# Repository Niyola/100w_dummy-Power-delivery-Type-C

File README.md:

USB Type-C Power Delivery Tester

A USB-C Power Delivery tester and 100W dummy load, built as part of my Master's thesis at Brno University of Technology.

The board negotiates a USB-PD contract with any USB-C charger, power bank, or laptop, requests different voltages (5V, 9V, 12V, 15V, 20V), and measures what is actually being delivered in real time. It handles up to 100W.

What's inside

The STM32F072CB runs the USB-PD protocol stack. The FUSB302B from onsemi handles the CC line communication. The INA237 from Texas Instruments measures voltage and current on VBUS bidirectionally. It is a 4-layer board, roughly 100mm by 60mm, with dedicated inner planes for ground and 3.3V.

References I used

Twonkie v2.0 by dojoe — https://github.com/dojoe/Twonkie/tree/master
An open source USB-PD sniffer. I followed its approach for the FUSB302B wiring and the CC line level shifting.

TI TPS25751EVM — https://www.ti.com/tool/TPS25751EVM
Texas Instruments' official USB-PD evaluation board. I used it as a reference for the high-current VBUS layout and current sensing.

What I changed

I use a single INA237 for bidirectional current sensing instead of two separate chips. I added a screw terminal output so the board works as a dummy load tester, not just a sniffer. I redesigned the stackup as 4 layers with full ground and 3.3V planes for better power integrity at 100W. I also added test points for bring-up.

About me

Eniola Adesuyi, M.Sc. Communications and Networking, Brno University of Technology. Supervised by Ing. Ondřej Krajsa, Ph.D.

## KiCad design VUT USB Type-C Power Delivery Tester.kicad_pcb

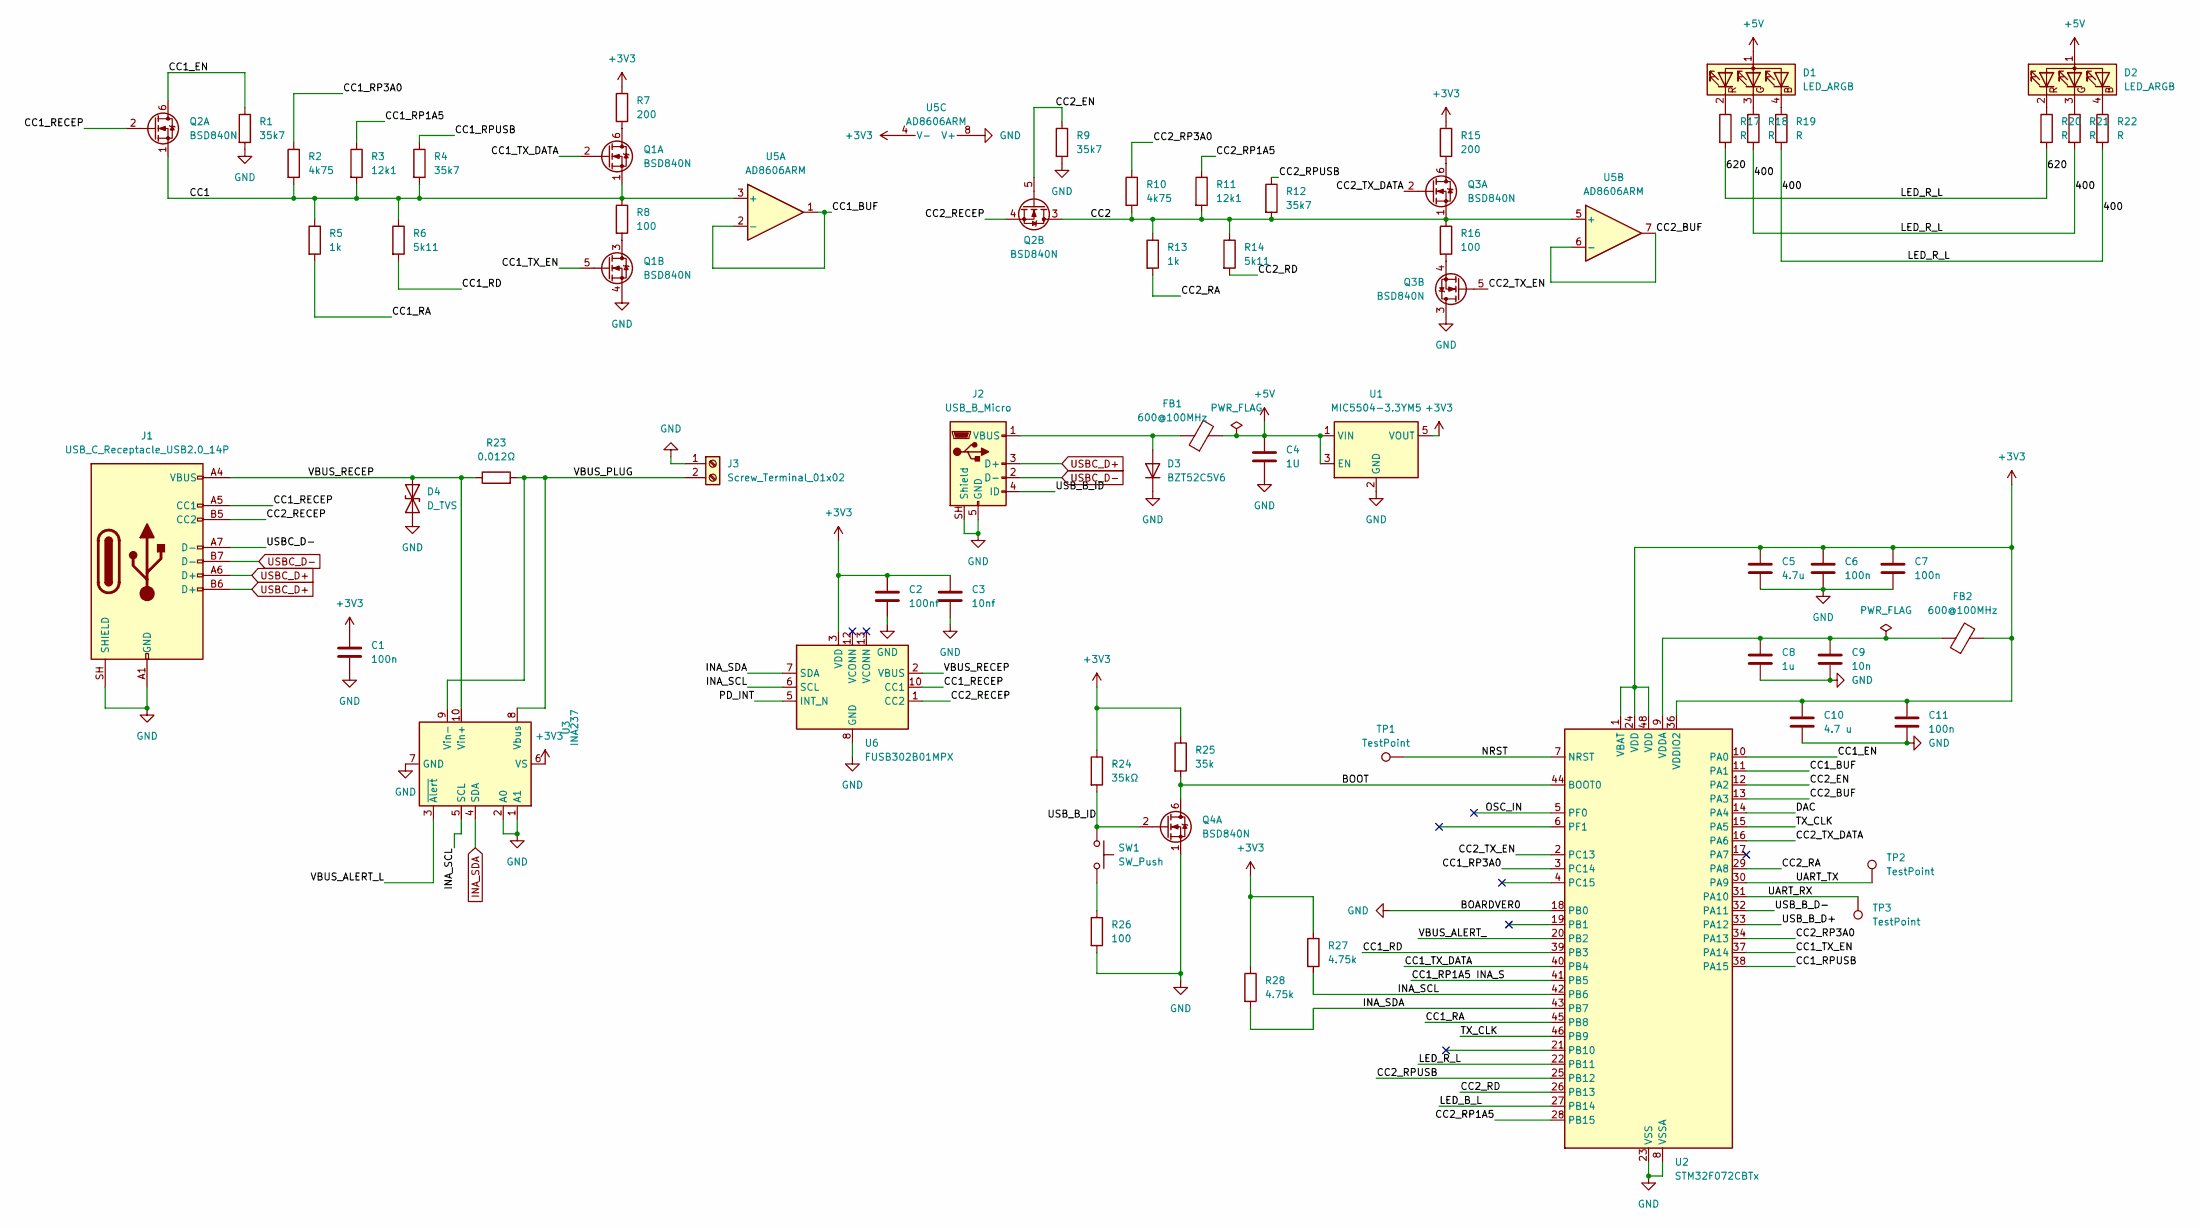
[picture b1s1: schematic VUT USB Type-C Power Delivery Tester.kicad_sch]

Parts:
C1, C6, C11: 100n; C_0402_1005Metric
C2: 100nf; C_0805_2012Metric
C3: 10nf; C_0402_1005Metric
C4: 1U; C_0402_1005Metric
C5: 4.7u; C_0402_1005Metric
C7: 100n; C_0805_2012Metric
C8: 1u; C_0402_1005Metric
C9: 10n; C_0402_1005Metric
C10: 4.7 u; C_0805_2012Metric
D1, D2: LED_ARGB; LED_Wurth_150044M155260
D3: BZT52C5V6; D_SOD-123
D4: D_TVS; D_SMB
FB1, FB2: 600@100MHz; L_0603_1608Metric
J1: USB_C_Receptacle_USB2.0_14P; USB_C_Receptacle_XKB_U262-16XN-4BVC11
J2: USB_B_Micro; USB_Micro-B_Molex-105017-0001
J3: Screw_Terminal_01x02; TerminalBlock_Phoenix_PT-1,5-2-3.5-H_1x02_P3.50mm_Horizontal
Q1, Q2, Q3, Q4: BSD840N; SOT-363_SC-70-6
R1, R4, R9, R12: 35k7; R_0402_1005Metric
R2, R10: 4k75; R_0402_1005Metric
R3, R11: 12k1; R_0402_1005Metric
R5, R13: 1k; R_0402_1005Metric
R6, R14: 5k11; R_0402_1005Metric
R7, R15: 200; R_0402_1005Metric
R8, R16, R26: 100; R_0402_1005Metric
R17, R18, R19, R20, R21, R22: R; R_0402_1005Metric
R23: 0.012Ω; R_0402_1005Metric
R24: 35kΩ; R_0402_1005Metric
R25: 35k; R_0402_1005Metric
R27, R28: 4.75k; R_0402_1005Metric
SW1: SW_Push; SW_SPST_PTS645Sx43SMTR92
TP1, TP2, TP3: TestPoint; TestPoint_Pad_1.0x1.0mm
U1: MIC5504-3.3YM5; SOT-23-5
U2: STM32F072CBTx; LQFP-48_7x7mm_P0.5mm
U3: INA237; TSSOP-10_3x3mm_P0.5mm
U5: AD8606ARM; MSOP-8_3x3mm_P0.65mm
U6: FUSB302B01MPX; WQFN-14-1EP_2.5x2.5mm_P0.5mm_EP1.45x1.45mm

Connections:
+3V3: C1.1, C2.1, C3.1, C5.1, C6.1, C7.1, C10.1, C11.1, FB2.2, R7.1, R15.1, R24.1, R25.1, R27.1, R28.1, U1.5 (VOUT), U2.1 (VBAT), U2.24 (VDD), U2.36 (VDDIO2), U2.48 (VDD), U3.6 (VS), U5.4 (V-), U6.3 (VDD), U6.4 (VDD)
+5V: C4.1, D1.1 (A), D2.1 (A), FB1.2, U1.1 (VIN), U1.3 (EN)
/400: R17.2, R18.2, R19.2, R20.2, R21.2, R22.2, U2.22 (PB11)
/BOOT: Q4.6 (D), R25.2, U2.44 (BOOT0)
/CC1: Q1.1 (S), Q2.1 (S), R2.2, R3.2, R4.2, R5.1, R6.1, R8.1, U5.3 (+)
/CC1_BUF: U2.11 (PA1), U5.1, U5.2 (-)
/CC1_EN: Q2.6 (D), R1.1, U2.10 (PA0)
/CC1_RA: R5.2, U2.45 (PB8)
/CC1_RD: R6.2, U2.39 (PB3)
/CC1_RECEP: J1.A5 (CC1), Q2.2 (G), U6.10 (CC1), U6.11 (CC1)
/CC1_RP1A5: R3.1
/CC1_RP1A5 INA_S: U2.41 (PB5)
/CC1_RP3A0: R2.1, U2.3 (PC14)
/CC1_RPUSB: R4.1, U2.38 (PA15)
/CC1_TX_DATA: Q1.2 (G), U2.40 (PB4)
/CC1_TX_EN: Q1.5 (G), U2.37 (PA14)
/CC2: Q2.3 (D), Q3.1 (S), R10.2, R11.2, R12.2, R13.1, R14.1, R16.1, U5.5 (+)
/CC2_BUF: U2.13 (PA3), U5.6 (-), U5.7
/CC2_EN: Q2.5 (G), R9.1, U2.12 (PA2)
/CC2_RA: R13.2, U2.29 (PA8)
/CC2_RD: R14.2, U2.26 (PB13)
/CC2_RECEP: J1.B5 (CC2), Q2.4 (S), U6.1 (CC2), U6.14 (CC2)
/CC2_RP1A5: R11.1, U2.28 (PB15)
/CC2_RP3A0: R10.1, U2.34 (PA13)
/CC2_RPUSB: R12.1, U2.25 (PB12)
/CC2_TX_DATA: Q3.2 (G), U2.16 (PA6)
/CC2_TX_EN: Q3.5 (G), U2.2 (PC13)
/DAC: U2.14 (PA4)
/INA_SCL: R27.2, U2.42 (PB6), U3.5 (SCL), U6.6 (SCL)
/LED_B_L: U2.27 (PB14)
/NRST: TP1.1 (1_1), U2.7 (NRST)
/OSC_IN: U2.5 (PF0)
/PD_INT: U6.5 (INT_N)
/TX_CLK: U2.15 (PA5), U2.46 (PB9)
/UART_RX: TP3.1 (1_1), U2.31 (PA10)
/UART_TX: TP2.1 (1_1), U2.30 (PA9)
/USB_B_D+: U2.33 (PA12)
/USB_B_D-: U2.32 (PA11)
/USB_B_ID: J2.4 (ID), Q4.2 (G), R24.2, SW1.1
/VBUS_ALERT_: U2.20 (PB2)
/VBUS_ALERT_L: U3.3 (~Alert)
/VBUS_PLUG: J3.2, R23.2, U3.8 (Vbus), U3.9 (Vin-)
/VBUS_RECEP: D4.1 (A1), J1.A4 (VBUS), J1.A9 (VBUS), J1.B4 (VBUS), J1.B9 (VBUS), R23.1, U3.10 (Vin+), U6.2 (VBUS)
GND: C1.2, C2.2, C3.2, C4.2, C5.2, C6.2, C7.2, C8.2, C9.2, C10.2, C11.2, D3.1 (K), D4.2 (A2), J1.A1 (GND), J1.A12 (GND), J1.B1 (GND), J1.B12 (GND), J1.SH (SHIELD), J2.5 (GND), J2.SH (Shield), J3.1, Q1.4 (S), Q3.3 (D), Q4.1 (S), R1.2, R9.2, R26.2, U1.2 (GND), U2.8 (VSSA), U2.18 (PB0), U2.23 (VSS), U2.35 (VSS), U2.47 (VSS), U3.1 (A1), U3.2 (A0), U3.7 (GND), U5.8 (V+), U6.8 (GND), U6.9 (GND), U6.15 (GND)
INA_SDA: R28.2, U2.43 (PB7), U3.4 (SDA), U6.7 (SDA)
unnamed: D1.4 (BK), R19.1
unnamed: D1.3 (GK), R18.1
unnamed: D1.2 (RK), R17.1
unnamed: D2.4 (BK), R22.1
unnamed: D2.3 (GK), R21.1
unnamed: D2.2 (RK), R20.1
unnamed: D3.2 (A), FB1.1, J2.1 (VBUS)
unnamed: Q1.6 (D), R7.2
unnamed: Q1.3 (D), R8.2
unnamed: Q3.6 (D), R15.2
unnamed: Q3.4 (S), R16.2
unnamed: R26.1, SW1.2
unnamed: C8.1, C9.1, FB2.1, U2.9 (VDDA)
USBC_D+: J1.A6 (D+), J1.B6 (D+), J2.3 (D+)
USBC_D-: J1.A7 (D-), J1.B7 (D-), J2.2 (D-)

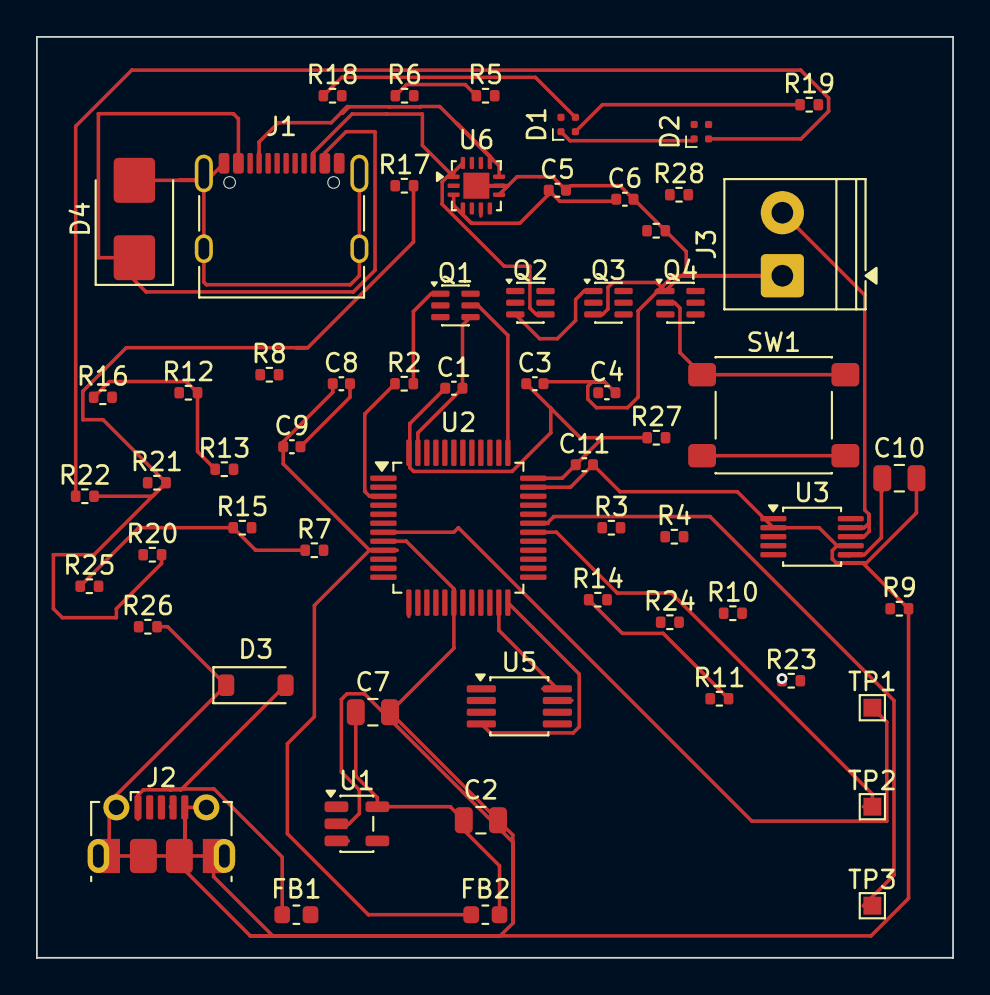
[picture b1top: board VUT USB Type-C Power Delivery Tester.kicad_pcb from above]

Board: 4 copper layers, 50.9 x 51.2 mm, 61 parts (0 on the bottom side), 50 nets.

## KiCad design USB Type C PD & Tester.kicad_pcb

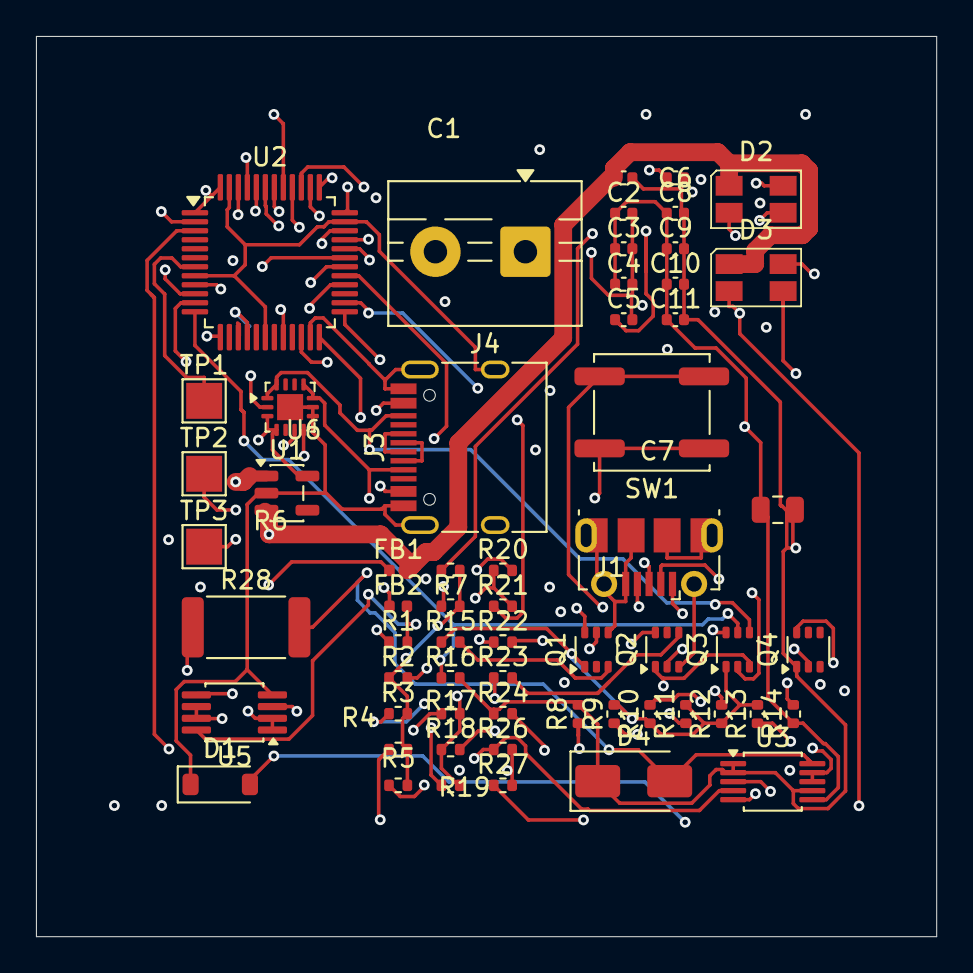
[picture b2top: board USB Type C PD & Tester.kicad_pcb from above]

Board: 4 copper layers, 50.0 x 50.0 mm, 60 parts (0 on the bottom side), 54 nets.

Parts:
C1, C5: 1u; C_0402_1005Metric
C2: 4.7u; C_0402_1005Metric
C3, C4, C8, C9: 100n; C_0402_1005Metric
C6: 10n; C_0402_1005Metric
C7: 4.7u; C_0805_2012Metric
C10: 100nF; C_0402_1005Metric
C11: 10nF; C_0402_1005Metric
D1: BZT52C5V6; D_SOD-123
D2, D3: LED_ARGB; LED_Avago_PLCC4_3.2x2.8mm_CW
D4: D_TVS; D_SMA
FB1, FB2: 600@100MHz; L_0402_1005Metric
J1: USB_B_Micro; USB_Micro-B_Molex-105017-0001
J3: USB_C_Receptacle_USB2.0_14P; USB_C_Receptacle_HRO_TYPE-C-31-M-12
J4: Screw_Terminal_01x02; TerminalBlock_MaiXu_MX126-5.0-02P_1x02_P5.00mm
Q1, Q2, Q3, Q4: BSD840N; SOT-363_SC-70-6
R1: 35k; R_0402_1005Metric
R2, R5: 620; R_0402_1005Metric
R3, R4, R6, R7: 400; R_0402_1005Metric
R8, R13, R16, R21: 35k7; R_0402_1005Metric
R9, R17: 4k75; R_0402_1005Metric
R10, R18: 1k; R_0402_1005Metric
R11, R19: 12k1; R_0402_1005Metric
R12, R20: 5k11; R_0402_1005Metric
R14, R22: 200; R_0402_1005Metric
R15, R23, R24: 100; R_0402_1005Metric
R26: 4.75k; R_0402_1005Metric
R27: 35kΩ; R_0402_1005Metric
R28: 0.012Ω; R_2512_6332Metric
SW1: SW_Push; SW_Push_1P1T_NO_CK_KSC6xxJ
TP1, TP2, TP3: TestPoint; TestPoint_Pad_2.0x2.0mm
U1: MIC5504-1.2YM5; SOT-23-5
U2: STM32F072CBTx; LQFP-48_7x7mm_P0.5mm
U3: INA237; VSSOP-10_3x3mm_P0.5mm
U5: AD8606ARM; MSOP-8_3x3mm_P0.65mm
U6: FUSB302B01MPX; WQFN-14-1EP_2.5x2.5mm_P0.5mm_EP1.45x1.45mm

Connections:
+3V3: C2.1, C3.1, C4.1, C7.1, C8.1, C9.1, C10.1, C11.1, FB2.2, R1.2, R14.1, R22.1, R26.2, R27.2, U1.5 (VOUT), U2.1 (VBAT), U2.24 (VDD), U2.36 (VDDIO2), U2.48 (VDD), U3.6 (VS), U5.8 (V+), U6.3 (VDD), U6.4 (VDD)
+5V: C1.1, D2.1 (A), D3.1 (A), FB1.2, U1.1 (VIN), U1.3 (EN)
/400: R2.1, R3.2, R4.2, R5.2, R6.2, R7.2, U2.22 (PB11)
/BOOT: Q4.6 (D), R1.1, U2.44 (BOOT0)
/CC1: Q1.1 (S), Q3.1 (S), R9.2, R10.1, R11.2, R12.1, R13.2, R15.1, U5.3 (+)
/CC1_BUF: U2.11 (PA1), U5.1, U5.2 (-)
/CC1_EN: Q3.6 (D), R8.1, U2.10 (PA0)
/CC1_RA: R10.2, U2.45 (PB8)
/CC1_RD: R12.2, U2.39 (PB3)
/CC1_RECEP: J3.A5 (CC1), Q3.2 (G), U6.10 (CC1), U6.11 (CC1)
/CC1_RP1A5: R11.1, U2.41 (PB5)
/CC1_RP3A0: R9.1, U2.3 (PC14)
/CC1_RPUSB: R13.1, U2.38 (PA15)
/CC1_TX_DATA: Q1.2 (G), U2.40 (PB4)
/CC1_TX_EN: Q1.5 (G), U2.37 (PA14)
/CC2: Q2.1 (S), Q3.3 (D), R17.2, R18.1, R19.2, R20.1, R21.2, R23.1, U5.5 (+)
/CC2_BUF: U2.13 (PA3), U5.6 (-), U5.7
/CC2_EN: Q3.5 (G), R16.1, U2.12 (PA2)
/CC2_RA: R18.2, U2.29 (PA8)
/CC2_RD: R20.2, U2.26 (PB13)
/CC2_RECEP: J3.B5 (CC2), Q3.4 (S), U6.1 (CC2), U6.14 (CC2)
/CC2_RP1A5: R19.1, U2.28 (PB15)
/CC2_RP3A0: R17.1, U2.34 (PA13)
/CC2_RPUSB: R21.1, U2.25 (PB12)
/CC2_TX_DATA: Q2.2 (G), U2.16 (PA6)
/CC2_TX_EN: Q2.5 (G), U2.2 (PC13)
/NRST: TP1.1, U2.7 (NRST)
/TX_CLK: U2.15 (PA5), U2.46 (PB9)
/UART_RX: TP3.1, U2.31 (PA10)
/UART_TX: TP2.1, U2.30 (PA9)
/VBUS_ALERT_L: U2.20 (PB2), U3.3 (~Alert)
/VBUS_PLUG: J4.2, R28.1, U3.8 (Vbus), U3.9 (Vin-)
/VBUS_RECEP: D4.2 (A2), J3.A4 (VBUS), J3.A9 (VBUS), J3.B4 (VBUS), J3.B9 (VBUS), R28.2, U3.10 (Vin+), U6.2 (VBUS)
GND: C1.2, C2.2, C3.2, C4.2, C5.2, C6.2, C7.2, C8.2, C9.2, C10.2, C11.2, D1.1 (K), D4.1 (A1), J1.5 (GND), J1.6 (Shield), J3.A1 (GND), J3.A12 (GND), J3.B1 (GND), J3.B12 (GND), J3.S1 (SHIELD), J4.1, Q1.4 (S), Q2.3 (D), Q4.1 (S), R8.2, R16.2, R24.1, U1.2 (GND), U2.8 (VSSA), U2.18 (PB0), U2.23 (VSS), U2.35 (VSS), U2.47 (VSS), U3.1 (A1), U3.2 (A0), U3.7 (GND), U5.4 (V-), U6.8 (GND), U6.9 (GND), U6.15 (GND)
INA_SCL: U2.42 (PB6), U3.5 (SCL), U6.6 (SCL)
INA_SDA: R26.1, U2.43 (PB7), U3.4 (SDA), U6.7 (SDA)
unnamed: D1.2 (A), FB1.1, J1.1 (VBUS)
unnamed: D2.4 (BK), R7.1
unnamed: D2.3 (GK), R6.1
unnamed: D2.2 (RK), R5.1
unnamed: D3.4 (BK), R4.1
unnamed: D3.3 (GK), R3.1
unnamed: D3.2 (RK), R2.2
unnamed: Q1.6 (D), R14.2
unnamed: Q1.3 (D), R15.2
unnamed: Q2.6 (D), R22.2
unnamed: Q2.4 (S), R23.2
unnamed: R24.2, SW1.1
unnamed: C5.1, C6.1, FB2.1, U2.9 (VDDA)
USBC_D+: J3.A6 (D+), J3.B6 (D+)
USBC_D-: J3.A7 (D-), J3.B7 (D-)
USB_B_D+: J1.3 (D+), U2.33 (PA12)
USB_B_D-: J1.2 (D-), U2.32 (PA11)
USB_B_ID: J1.4 (ID), Q4.2 (G), R27.1, SW1.2

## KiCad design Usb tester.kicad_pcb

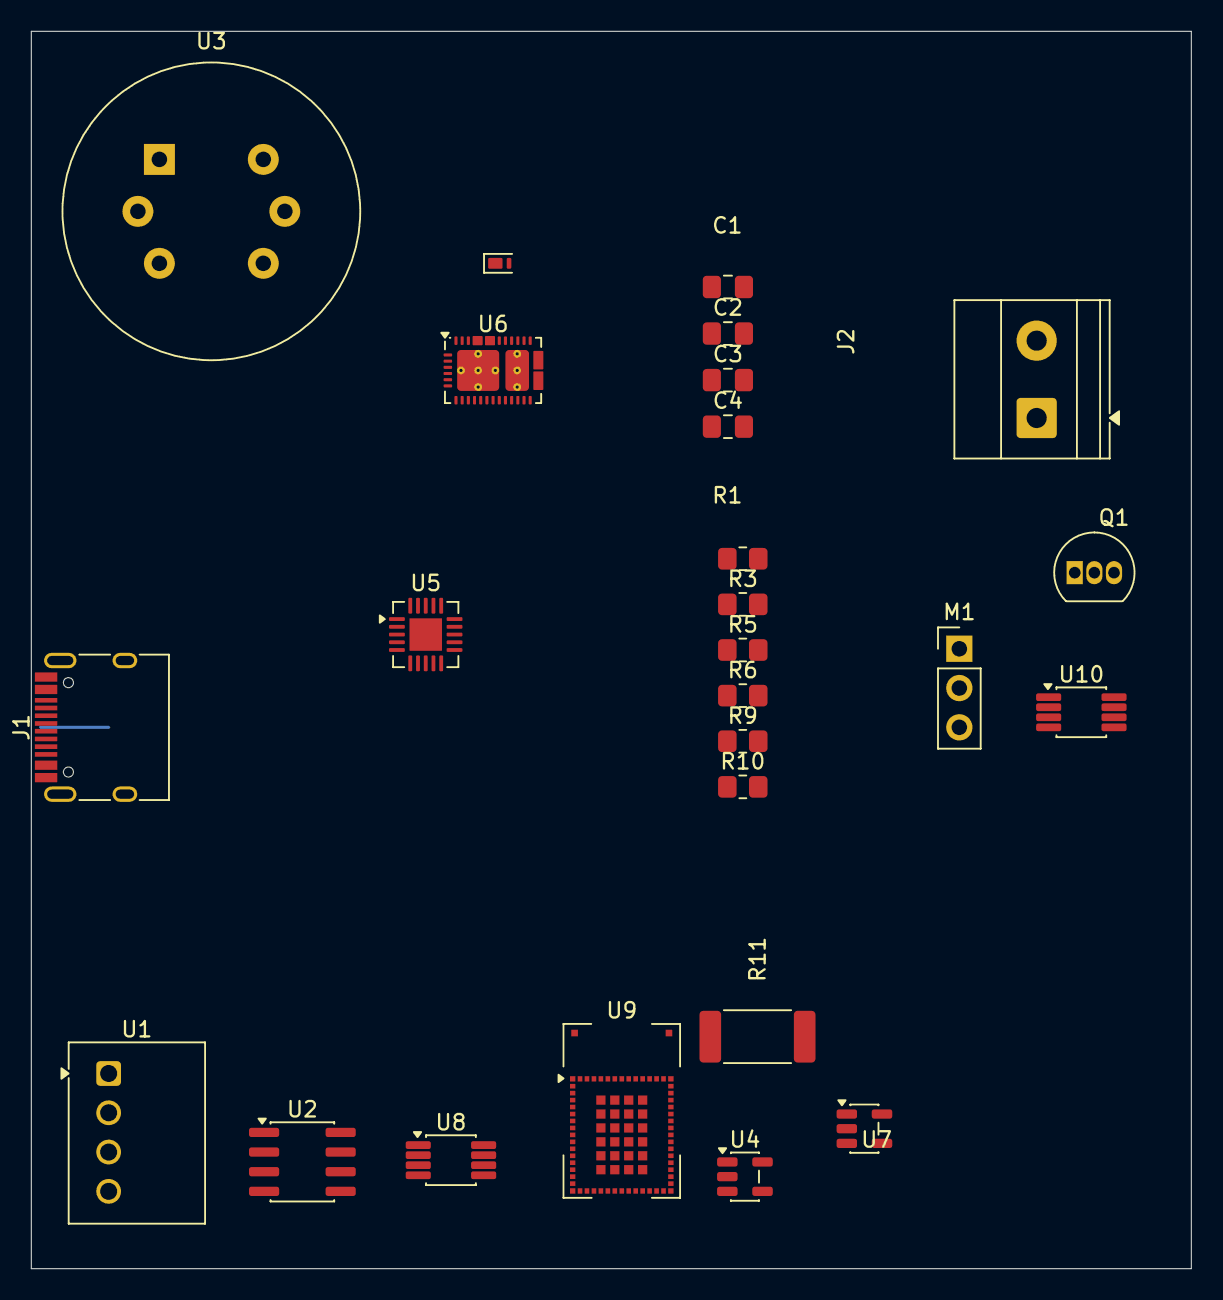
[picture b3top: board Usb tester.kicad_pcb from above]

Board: 2 copper layers, 75.0 x 80.0 mm, 26 parts (0 on the bottom side), 20 nets.

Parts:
C1, C2, C3: C; C_0805_2012Metric_Pad1.18x1.45mm_HandSolder
C4: 1µF; C_0805_2012Metric_Pad1.18x1.45mm_HandSolder
D2: PTVS5V0Z1USK; Nexperia_DSN1608-2_1.6x0.8mm
J1: USB_C_Receptacle_USB2.0_16P; USB_C_Receptacle_HRO_TYPE-C-31-M-12
J2: Screw_Terminal_01x02; TerminalBlock_Phoenix_MKDS-1,5-2_1x02_P5.00mm_Horizontal
M1: Fan; PinHeader_1x03_P2.54mm_Vertical
Q1: BF244A; TO-92_Inline
R1, R3, R5, R6, R9, R10: R; R_0805_2012Metric_Pad1.20x1.40mm_HandSolder
R11: R_Shunt; R_2512_6332Metric_Pad1.40x3.35mm_HandSolder
U1: TMU3-0511; Converter_DCDC_TRACO_TMU3-05xx_12xx_THT
U2: CAP200DG; SOIC-8_3.9x4.9mm_P1.27mm
U3: MQ-6
U4, U7: INA180A1; SOT-23-5
U5: TCPP03-M20; TQFN-20-1EP_4x4mm_P0.5mm_EP2.1x2.1mm
U6: TPS25730D; Texas_REF0038A_WQFN-38-2EP_6x4mm_P0.4
U8, U10: ADC082S021; VSSOP-8_3x3mm_P0.65mm
U9: STM32WB5MMG; ST-SiP-LGA-86-11x7.3mm

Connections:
+5V: C1.1, C1.2, C3.1, C3.2, J1.A1 (GND), J1.A12 (GND), J1.B1 (GND), J1.B8 (SBU2), J1.B12 (GND), J1.S1 (SHIELD), Q1.3 (S), R1.1, R6.2, R9.1, R9.2, U1.3 (-Vout), U1.4 (+Vout), U2.6, U2.7, U3.4 (A2), U3.6 (A1), U4.2 (GND), U4.3 (+), U4.4 (-), U5.3 (CC2), U5.12 (GND), U5.13 (CC2_{c}), U5.14 (C_{BIAS}), U5.15 (CC1_{c}), U5.16 (I2C_{ADD}), U5.17 (SDA), U5.18 (SCL), U5.20 (EN), U5.21 (GND), U6.5 (ADCIN3), U6.15 (DRAIN), U6.30 (DRAIN), U6.38 (VIN_3V3), U6.40 (DRAIN), U7.2 (GND), U7.5 (V+), U8.3 (GND), U8.4 (IN2), U8.7 (DOUT)
unnamed: J2.1, U3.1 (B1)
unnamed: J2.2, U3.3 (B2), U9.4 (VREF), U9.6 (VDDA), U9.13 (PH3-BOOT0), U9.15 (VBAT), U9.17 (VDDSMPS), U9.32 (VDDUSB)
unnamed: M1.1 (+), R10.2, R11.1, U8.5 (IN1)
unnamed: M1.2 (-), U7.1
unnamed: Q1.1 (D), U1.2 (+Vin), U5.2 (VCC_{VCONN}), U10.2 (V_{A})
unnamed: R5.1, U4.1
unnamed: U1.1 (-Vin), U5.1 (CC1), U6.28 (CC1), U6.29 (CC2), U10.3 (GND), U10.5 (IN1), U10.7 (DOUT)
unnamed: U2.5, U2.8
unnamed: U2.2, U2.3, U2.4, U3.5 (VH-), U6.9 (I2Ct_SCL), U6.18 (~FAULT_IN), U6.36 (RESERVED), U9.33 (PD0), U9.68 (PD2), U9.77 (PD10), U9.80 (PD5)
unnamed: R3.2, U4.5 (V+)
unnamed: C4.1, U6.4 (LDO_1V5)
unnamed: R6.1, U7.3 (+)
unnamed: R5.2, U7.4 (-)
unnamed: U8.6 (DIN), U8.8 (SCLK)
unnamed: U2.1, U6.11 (GND), U6.12 (GND), U6.14 (GND), U6.16 (GND), U6.17 (GND), U6.31 (GND), U6.34 (GND), U6.39 (GND), U8.2 (V_{A})
unnamed: C4.2, U9.42 (PE4)
unnamed: U10.6 (DIN), U10.8 (SCLK)
VBUS: C2.1, C2.2, D2.1 (K), D2.2 (A), J1.A4 (VBUS), J1.A5 (CC1), J1.A6 (D+), J1.A7 (D-), J1.A8 (SBU1), J1.A9 (VBUS), J1.B4 (VBUS), J1.B5 (CC2), J1.B6 (D+), J1.B7 (D-), J1.B9 (VBUS), R10.1, U5.9 (VBUS_{c}), U5.10 (I_{sense}), U5.11 (V_{sense}), U6.20 (PPHV)
VCC: R1.2, R3.1, U3.2 (VH+), U8.1 (~CS), U10.1 (~CS)

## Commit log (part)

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2026-02-18 New Board
